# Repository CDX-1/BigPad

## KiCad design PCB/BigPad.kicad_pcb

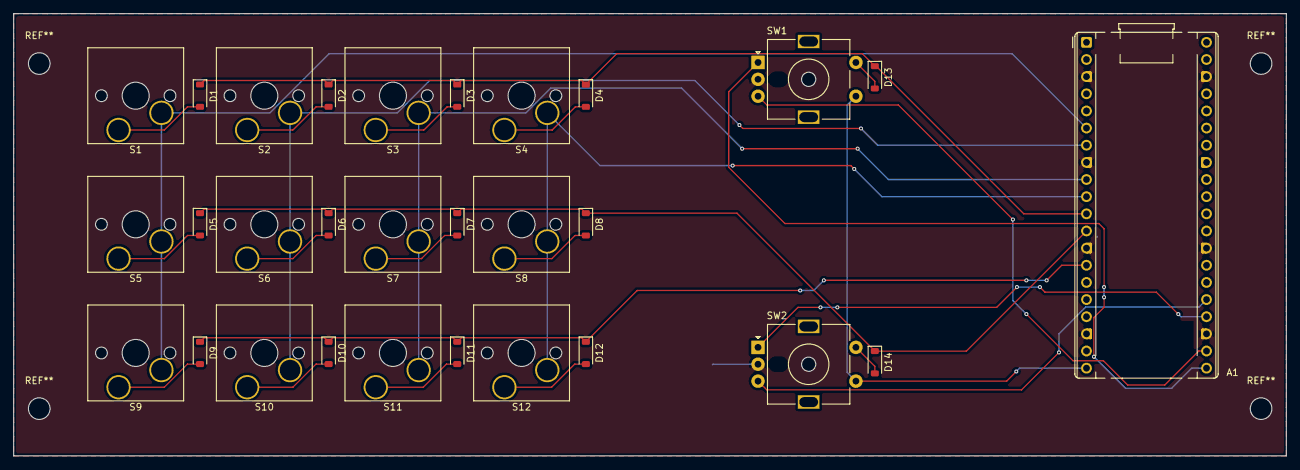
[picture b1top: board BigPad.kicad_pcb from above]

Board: 2 copper layers, 188.5 x 65.5 mm, 29 parts (0 on the bottom side), 27 nets.

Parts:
A1: RaspberryPi_Pico; RaspberryPi_Pico_Common_THT
D1, D2, D3, D4, D5, D6, D7, D8, D9, D10, D11, D12, D13, D14: D_SOD-123
S1, S2, S3, S4, S5, S6, S7, S8, S9, S10, S11, S12: SW_Hotswap_Kailh_MX_Plated_1.00u
SW1, SW2: RotaryEncoder_Switch; RotaryEncoder_Alps_EC11E-Switch_Vertical_H20mm_MountingHoles

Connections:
/Column 0: A1.6 (GPIO4), S1.1, S5.1, S9.1
/Column 1: A1.7 (GPIO5), S2.1, S6.1, S10.1
/Column 2: A1.9 (GPIO6), S3.1, S7.1, S11.1
/Column 3: A1.10 (GPIO7), S4.1, S8.1, S12.1
/Column 4: A1.20 (GPIO15), SW1.S1, SW2.S1
/Row 0: A1.11 (GPIO8), D1.1 (K), D2.1 (K), D3.1 (K), D4.1 (K), D13.1 (K)
/Row 1: A1.12 (GPIO9), D5.1 (K), D6.1 (K), D7.1 (K), D8.1 (K), D14.1 (K)
/Row 2: A1.14 (GPIO10), D9.1 (K), D10.1 (K), D11.1 (K), D12.1 (K)
GND: A1.3 (GND), A1.8 (GND), A1.13 (GND), A1.18 (GND), A1.23 (GND), A1.28 (GND), A1.38 (GND), SW1.C, SW2.C
unnamed: A1.21 (GPIO16), SW1.A
unnamed: A1.22 (GPIO17), SW1.B
unnamed: A1.24 (GPIO18), SW2.A
unnamed: A1.25 (GPIO19), SW2.B
unnamed: D1.2 (A), S1.2
unnamed: D2.2 (A), S2.2
unnamed: D3.2 (A), S3.2
unnamed: D4.2 (A), S4.2
unnamed: D5.2 (A), S5.2
unnamed: D6.2 (A), S6.2
unnamed: D7.2 (A), S7.2
unnamed: D8.2 (A), S8.2
unnamed: D9.2 (A), S9.2
unnamed: D10.2 (A), S10.2
unnamed: D11.2 (A), S11.2
unnamed: D12.2 (A), S12.2
unnamed: D13.2 (A), SW1.S2
unnamed: D14.2 (A), SW2.S2

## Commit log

2026-05-20 BigPad KiCad
2026-05-21 Removed unnecessary ZIP
2026-05-21 update git ignore
2026-05-21 Updated rotary encoder wiring in schematic
2026-05-21 completed rotary encoders in PCB design
2026-05-21 added m3 screw holes to pcb
2026-05-23 fixed several wiring issues
